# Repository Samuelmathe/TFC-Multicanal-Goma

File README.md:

# TFC Multicanal Goma

Système embarqué IoT de sous-comptage électrique multicanal (ESP32),
développé dans le cadre d'un Travail de Fin de Cycle (ULPGL) : un boîtier
mesure et facture séparément la consommation électrique de plusieurs
locataires branchés sur une même installation, avec coupure automatique par
crédit prépayé et consultation via une application mobile Flutter.

## État du projet

- **Maquette physique** : construite, soudée sur carte perforée et
  **validée sur matériel réel** (4 canaux : 1 bailleur + 3 locataires,
  capteurs simulés par des potentiomètres). C'est cette maquette qui a servi
  à la validation présentée dans le mémoire.
- **Application mobile Flutter** : développée et testée en conditions
  réelles (connexion Wi-Fi à l'ESP32 depuis un téléphone Android).
- **PCB (circuit imprimé, 8 canaux, capteurs ACS712/ZMPT101B réels)** :
  conçu et **routé** sous KiCad (dossier `kicad/`). Carte **compactée le
  19/11/2026 : 138 x 349,5 mm** au lieu de 260 x 440 mm (−58 % de surface),
  re-routée avec Freerouting (scripts `kicad/tools/compact_pcb.py`,
  `route_pcb.py`, `finish_acs712.py`, `cleanup_after_route.py`). Les 17
  borniers restent sur le bord droit ; le HLK-PM01 et le ZMPT101B sont
  regroupés près de l'entrée secteur J10.
  Ajouts du 19/11/2026 : ponts diviseurs 10 k / 12 k (R6-R23) entre les
  capteurs 5 V et les entrées ADC de l'ESP32 ; 32 points d'accueil pour les
  barres de cuivre qui portent le courant de puissance (20 A) ; entrée
  secteur du ZMPT101B déportée sur un bornier J27 au pas de 5 mm (le
  connecteur U12 ne porte plus que GND / VCC / OUT).
  Dernier DRC (KiCad 10.0.8, 19/11/2026) : **0 élément non connecté**,
  7 violations, toutes cosmétiques (empreintes modifiées localement) ;
  plus aucun écart de dégagement 230 V. Détails : `kicad/COMPACTAGE_PCB.md`.
  Les liaisons très proches sur les broches du ACS712 sont couvertes par
  `multical.kicad_dru` (les deux côtés du shunt sont au même potentiel).
  **Non fabriqué ni assemblé** : les Gerbers de `kicad/multical/fabrication/`
  ont été régénérés pour la carte compacte. Le firmware cible
  (`firmware_pcb_capteurs_reels/`) est écrit et compile, mais n'a pas pu
  être testé sur matériel réel.
- **Boîtier 3D** (`boitier/multicanal_boitier.scad`, OpenSCAD) : boîtier
  paramétrique pour le PCB, avec rampe inclinée sur les borniers et
  étiquettes gravées (BAI, LOC1 à LOC7, NEUTRE). Cotes mises à jour pour la
  carte compacte.

## Structure du dépôt

```
firmware/                      -> firmware de la maquette physique (4 canaux,
                                   potentiometres) - construit et valide
firmware_pcb_capteurs_reels/    -> firmware cible pour le PCB (8 canaux,
                                    ACS712 + ZMPT101B) - PCB pas encore
                                    fabrique, code non teste sur materiel reel
application/                     -> application mobile Flutter (Android/iOS)
kicad/                            -> conception du circuit imprime (PCB, 8 canaux)
boitier/                          -> boitier 3D du PCB (OpenSCAD)
rapport/                           -> memoire de TFC
presentation/                       -> support de soutenance
```

Chaque dossier de firmware a son propre `README.md` avec le détail de ce qui
a été testé ou non.

## Démarrer

- Firmware maquette : `cd firmware && pio run --target upload` (ESP32 branché
  en USB) — voir `GUIDE_ASSEMBLAGE_ET_FLASH.md` et `GUIDE_MAQUETTE_BOITIER.md`
  à la racine pour le montage physique.
- Application mobile : `cd application && flutter run` (ou `build_apk.sh`
  pour générer un APK).

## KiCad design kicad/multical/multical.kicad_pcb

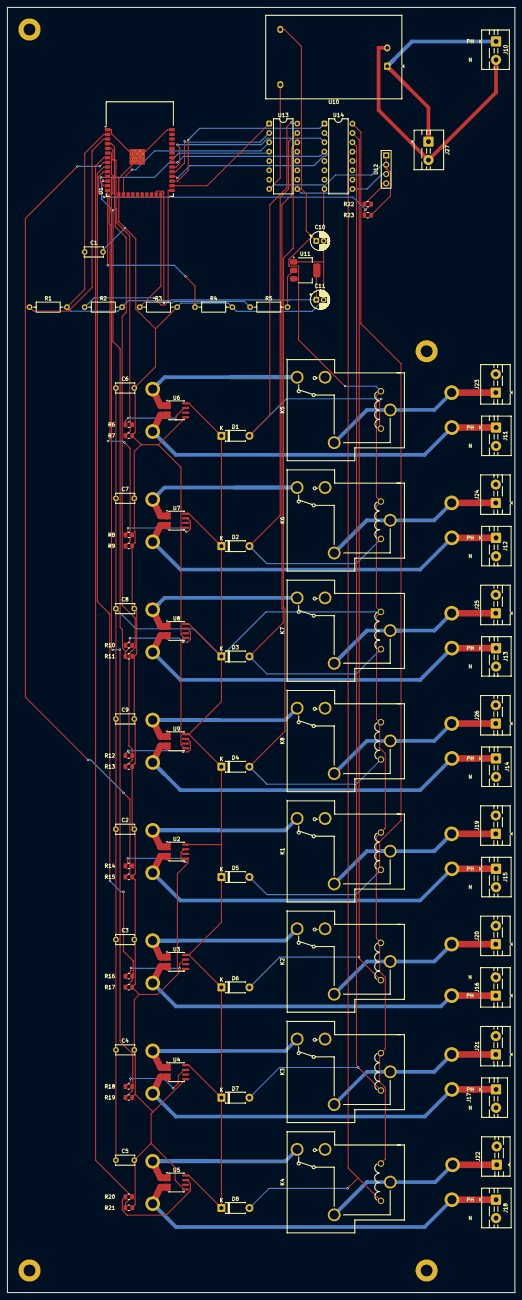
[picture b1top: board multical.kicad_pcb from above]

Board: 2 copper layers, 138.0 x 349.5 mm, 118 parts (0 on the bottom side), 68 nets.

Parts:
BAR1, BAR2, BAR3, BAR4, BAR5, BAR6, BAR7, BAR8, BAR9, BAR10, BAR11, BAR12, BAR13, BAR14, BAR15, BAR16, BAR17, BAR18, BAR19, BAR20, BAR21, BAR22, BAR23, BAR24, BAR25, BAR26, BAR27, BAR28, BAR29, BAR30, BAR31, BAR32: Point barre cuivre; Point_barre_cuivre
C1, C2, C3, C4, C5, C6, C7, C8, C9: C; C_Disc_D5.0mm_W2.5mm_P5.00mm
C10, C11: C; CP_Radial_D5.0mm_P2.00mm
D1, D2, D3, D4, D5, D6, D7, D8: D; D_DO-41_SOD81_P7.62mm_Horizontal
J10, J11, J12, J13, J14, J15, J16, J17, J18, J19, J20, J21, J22, J23, J24, J25, J26: Screw_Terminal_01x02; TerminalBlock_MaiXu_MX126-5.0-02P_1x02_P5.00mm
J27: ZMPT_secteur; TerminalBlock_MaiXu_MX126-5.0-02P_1x02_P5.00mm
K1, K2, K3, K4, K5, K6, K7, K8: Songle_SLA-05VDC-SL-C_LCSC-C87367; RELAY-TH_SLA-XXVDC-XX-C
MH1, MH2, MH3, MH4: MountingHole_3.2mm; MountingHole_3.2mm_NPTH
R1, R2, R3, R4, R5: R; R_Axial_DIN0207_L6.3mm_D2.5mm_P10.16mm_Horizontal
R6, R8, R10, R12, R14, R16, R18, R20, R22: 10k; R_0805_2012Metric
R7, R9, R11, R13, R15, R17, R19, R21, R23: 12k; R_0805_2012Metric
U1: ESP32-WROOM-32
U2, U3, U4, U5, U6, U7, U8, U9: ACS712xLCTR-20A; SOIC-8_3.9x4.9mm_P1.27mm
U10: HLK-PM01; Converter_ACDC_Hi-Link_HLK-PMxx
U11: AMS1117-3.3; SOT-223-3_TabPin2
U12: zmpt101b; ZMPT101B_Header_1x04
U13, U14: ULN2003A; DIP-16_W7.62mm

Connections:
/ACS1_VOUT: R6.1, U6.7 (VIOUT)
/ACS2_VOUT: R8.1, U7.7 (VIOUT)
/ACS3_VOUT: R10.1, U8.7 (VIOUT)
/ACS4_VOUT: R12.1, U9.7 (VIOUT)
/ACS5_VOUT: R14.1, U2.7 (VIOUT)
/ACS6_VOUT: R16.1, U3.7 (VIOUT)
/ACS7_VOUT: R18.1, U4.7 (VIOUT)
/ACS8_VOUT: R20.1, U5.7 (VIOUT)
/CANAL1_HT: BAR1.1, K5.12, U6.1 (IP+), U6.2 (IP+)
/CANAL1_OUT: BAR2.1, BAR4.1, J11.1, U6.3 (IP-), U6.4 (IP-)
/CANAL2_HT: BAR5.1, K6.12, U7.1 (IP+), U7.2 (IP+)
/CANAL2_OUT: BAR6.1, BAR8.1, J12.1, U7.3 (IP-), U7.4 (IP-)
/CANAL3_HT: BAR9.1, K7.12, U8.1 (IP+), U8.2 (IP+)
/CANAL3_OUT: BAR10.1, BAR12.1, J13.1, U8.3 (IP-), U8.4 (IP-)
/CANAL4_HT: BAR13.1, K8.12, U9.1 (IP+), U9.2 (IP+)
/CANAL4_OUT: BAR14.1, BAR16.1, J14.1, U9.3 (IP-), U9.4 (IP-)
/CANAL5_HT: BAR17.1, K1.12, U2.1 (IP+), U2.2 (IP+)
/CANAL5_OUT: BAR18.1, BAR20.1, J15.1, U2.3 (IP-), U2.4 (IP-)
/CANAL6_HT: BAR21.1, K2.12, U3.1 (IP+), U3.2 (IP+)
/CANAL6_OUT: BAR22.1, BAR24.1, J16.1, U3.3 (IP-), U3.4 (IP-)
/CANAL7_HT: BAR25.1, K3.12, U4.1 (IP+), U4.2 (IP+)
/CANAL7_OUT: BAR26.1, BAR28.1, J17.1, U4.3 (IP-), U4.4 (IP-)
/CANAL8_HT: BAR29.1, K4.12, U5.1 (IP+), U5.2 (IP+)
/CANAL8_OUT: BAR30.1, BAR32.1, J18.1, U5.3 (IP-), U5.4 (IP-)
/EN: R1.1, U1.3 (EN)
/GND: C1.2, C2.2, C3.2, C4.2, C5.2, C6.2, C7.2, C8.2, C9.2, C10.2, C11.2, R3.2, R4.2, R7.2, R9.2, R11.2, R13.2, R15.2, R17.2, R19.2, R21.2, R23.2, U1.1 (GND), U1.15 (GND), U1.38 (GND), U1.39 (GND), U2.5 (GND), U3.5 (GND), U4.5 (GND), U5.5 (GND), U6.5 (GND), U7.5 (GND), U8.5 (GND), U9.5 (GND), U10.3 (-Vout), U11.1 (GND), U12.3, U12.4, U13.8 (GND), U14.8 (GND)
/GPIO4: U1.26 (IO4), U13.1 (I1)
/GPIO5: U1.29 (IO5), U13.2 (I2)
/GPIO13: U1.16 (IO13), U13.3 (I3)
/GPIO14: U1.13 (IO14), U13.4 (I4)
/GPIO16: U1.27 (IO16), U14.1 (I1)
/GPIO17: U1.28 (IO17), U14.2 (I2)
/GPIO18: U1.30 (IO18), U14.3 (I3)
/GPIO19: U1.31 (IO19), U14.4 (I4)
/GPIO25: R22.2, R23.1, U1.10 (IO25)
/GPIO26: R8.2, R9.1, U1.11 (IO26)
/GPIO27: R10.2, R11.1, U1.12 (IO27)
/GPIO32: R14.2, R15.1, U1.8 (IO32)
/GPIO33: R16.2, R17.1, U1.9 (IO33)
/GPIO34: R18.2, R19.1, U1.6 (IO34)
/GPIO35: R20.2, R21.1, U1.7 (IO35)
/GPIO36: R6.2, R7.1, U1.4 (SENSOR_VP)
/GPIO39: R12.2, R13.1, U1.5 (SENSOR_VN)
/IO0: R2.1, U1.25 (IO0)
/IO2: R3.1, U1.24 (IO2)
/IO12: R4.1, U1.14 (IO12)
/IO15: R5.1, U1.23 (IO15)
/NEUTRE_BUS: J10.2, J27.2, U10.2 (AC/N)
/P3V3: C1.1, C11.1, R1.2, R2.2, R5.2, U1.2 (VDD), U11.2 (VO)
/P5V: C2.1, C3.1, C4.1, C5.1, C6.1, C7.1, C8.1, C9.1, C10.1, D1.1 (K), D2.1 (K), D3.1 (K), D4.1 (K), D5.1 (K), D6.1 (K), D7.1 (K), D8.1 (K), K1.A1, K2.A1, K3.A1, K4.A1, K5.A1, K6.A1, K7.A1, K8.A1, U2.8 (VCC), U3.8 (VCC), U4.8 (VCC), U5.8 (VCC), U6.8 (VCC), U7.8 (VCC), U8.8 (VCC), U9.8 (VCC), U10.4 (+Vout), U11.3 (VI), U12.5, U13.9 (COM), U14.9 (COM)
/PHASE_BUS: J10.1, J27.1, U10.1 (AC/L)
/REL1_DRV: D1.2 (A), K5.A2, U13.16 (O1)
/REL2_DRV: D2.2 (A), K6.A2, U13.15 (O2)
/REL3_DRV: D3.2 (A), K7.A2, U13.14 (O3)
/REL4_DRV: D4.2 (A), K8.A2, U13.13 (O4)
/REL5_DRV: D5.2 (A), K1.A2, U14.16 (O1)
/REL6_DRV: D6.2 (A), K2.A2, U14.15 (O2)
/REL7_DRV: D7.2 (A), K3.A2, U14.14 (O3)
/REL8_DRV: D8.2 (A), K4.A2, U14.13 (O4)
/ZMPT_VOUT: R22.1, U12.6
CANAL1_PHASE_IN: BAR3.1, J23.1, K5.11
CANAL2_PHASE_IN: BAR7.1, J24.1, K6.11
CANAL3_PHASE_IN: BAR11.1, J25.1, K7.11
CANAL4_PHASE_IN: BAR15.1, J26.1, K8.11
CANAL5_PHASE_IN: BAR19.1, J19.1, K1.11
CANAL6_PHASE_IN: BAR23.1, J20.1, K2.11
CANAL7_PHASE_IN: BAR27.1, J21.1, K3.11
CANAL8_PHASE_IN: BAR31.1, J22.1, K4.11

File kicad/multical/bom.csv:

"Références","Valeur","Empreinte","Qté"
"C1-C9","100n","Capacitor_THT:C_Disc_D5.0mm_W2.5mm_P5.00mm","9"
"C10,C11","100n","Capacitor_THT:CP_Radial_D5.0mm_P2.00mm","2"
"D1-D8","D","Diode_THT:D_DO-41_SOD81_P7.62mm_Horizontal","8"
"J10-J17,J19-J26","Screw_Terminal_01x02","TerminalBlock:TerminalBlock_MaiXu_MX126-5.0-02P_1x02_P5.00mm","16"
"J18","Screw_Terminal_01x02","TerminalBlock_MaiXu_MX126-5.0-02P_1x02_P5.00mm","1"
"K1-K8","Songle_SLA-05VDC-SL-C_LCSC-C87367","multical_local:RELAY-TH_SLA-XXVDC-XX-C","8"
"R1-R5","10k","Resistor_THT:R_Axial_DIN0207_L6.3mm_D2.5mm_P10.16mm_Horizontal","5"
"U1","ESP32-WROOM-32","RF_Module:ESP32-WROOM-32","1"
"U2-U9","ACS712xLCTR-20A","Package_SO:SOIC-8_3.9x4.9mm_P1.27mm","8"
"U10","HLK-PM01","Converter_ACDC:Converter_ACDC_Hi-Link_HLK-PMxx","1"
"U11","AMS1117-3.3","Package_TO_SOT_SMD:SOT-223-3_TabPin2","1"
"U12","zmpt101b","Connector_PinHeader_2.54mm:PinHeader_1x06_P2.54mm_Vertical","1"
"U13,U14","ULN2003A","Package_DIP:DIP-16_W7.62mm","2"

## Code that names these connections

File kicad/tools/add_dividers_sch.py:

"""Ajoute au schema les ponts diviseurs 10 k / 12 k entre les sorties des
capteurs (alimentes en 5 V) et les entrees ADC de l'ESP32.

Pour chaque capteur : l'etiquette posee sur sa broche de sortie (GPIOxx) est
renommee ACSn_VOUT (ou ZMPT_VOUT) ; deux resistances sont ajoutees dans le bas
de la feuille, reliees par etiquettes :
    ACSn_VOUT --[10k]-- GPIOxx --[12k]-- GND
Rapport 12/22 : 0,5-4,5 V -> 0,27-2,45 V (plage utile de l'ADC a 12 dB).
"""
import re, uuid
from pathlib import Path

SCH = Path(__file__).resolve().parents[1] / "multical" / "multical.kicad_sch"
ROOT_UUID = "58486ab8-8a77-40bd-879b-8044d35a44e6"
FOOTPRINT = "Resistor_SMD:R_0805_2012Metric"

# (capteur, etiquette actuelle sur la broche de sortie (x, y), nouveau nom)
SENSORS = [
    ("U6", "GPIO36", (58.42, 50.8), "ACS1_VOUT"),
    ("U7", "GPIO26", (57.15, 76.2), "ACS2_VOUT"),
    ("U8", "GPIO27", (59.69, 96.52), "ACS3_VOUT"),
    ("U9", "GPIO39", (62.23, 116.84), "ACS4_VOUT"),
    ("U2", "GPIO32", (101.6, 49.53), "ACS5_VOUT"),
    ("U3", "GPIO33", (101.6, 72.39), "ACS6_VOUT"),
    ("U4", "GPIO34", (101.6, 95.25), "ACS7_VOUT"),
    ("U5", "GPIO35", (101.6, 118.11), "ACS8_VOUT"),
    ("U12", "GPIO25", (185.42, 149.86), "ZMPT_VOUT"),
]

s = SCH.read_text(encoding="utf-8")
assert "ACS1_VOUT" not in s, "deja applique"
u = lambda: str(uuid.uuid4())


def fmt(v):
    return f"{v:.2f}".rstrip("0").rstrip(".")


# 1) renommage des etiquettes cote capteur
for ref, old, (x, y), new in SENSORS:
    pat = re.compile(r'\(label "' + old + r'"\s+\(at ' + re.escape(fmt(x)) + r" " + re.escape(fmt(y)) + r" ")
    m = pat.search(s)
    assert m, (ref, old, x, y)
    s = s[:m.start()] + f'(label "{new}"\n\t\t(at {fmt(x)} {fmt(y)} ' + s[m.end():]


def label(name, x, y, angle=0):
    return (f'\t(label "{name}"\n\t\t(at {fmt(x)} {fmt(y)} {angle})\n\t\t(effects\n\t\t\t(font\n\t\t\t\t(size 1.27 1.27)\n'
            f'\t\t\t)\n\t\t\t(justify left)\n\t\t)\n\t\t(uuid "{u()}")\n\t)\n')


def prop(name, value, x, y, hide=False, angle=0, justify=True):
    return (f'\t\t(property "{name}" "{value}"\n\t\t\t(at {fmt(x)} {fmt(y)} {angle})\n'
            + ("\t\t\t(hide yes)\n" if hide else "")
            + '\t\t\t(show_name no)\n\t\t\t(do_not_autoplace no)\n\t\t\t(effects\n\t\t\t\t(font\n\t\t\t\t\t(size 1.27 1.27)\n\t\t\t\t)\n'
            + ("\t\t\t\t(justify left)\n" if justify else "") + "\t\t\t)\n\t\t)\n")


def resistor(ref, value, x, y):
    return ("\t(symbol\n\t\t(lib_id \"Device:R\")\n" f"\t\t(at {fmt(x)} {fmt(y)} 0)\n"
            "\t\t(unit 1)\n\t\t(body_style 1)\n\t\t(exclude_from_sim no)\n\t\t(in_bom yes)\n\t\t(on_board yes)\n"
            "\t\t(in_pos_files yes)\n\t\t(dnp no)\n\t\t(fields_autoplaced yes)\n" f"\t\t(uuid \"{u()}\")\n"
            + prop("Reference", ref, x + 2.54, y - 1.27)
            + prop("Value", value, x + 2.54, y + 1.27)
            + prop("Footprint", FOOTPRINT, x - 1.778, y, hide=True, angle=90, justify=False)
            + prop("Datasheet", "", x, y, hide=True, justify=False)
            + prop("Description", "Resistor", x, y, hide=True, justify=False)
            + f'\t\t(pin "2"\n\t\t\t(uuid "{u()}")\n\t\t)\n\t\t(pin "1"\n\t\t\t(uuid "{u()}")\n\t\t)\n'
            f'\t\t(instances\n\t\t\t(project "multical"\n\t\t\t\t(path "/{ROOT_UUID}"\n\t\t\t\t\t(reference "{ref}")\n'
            "\t\t\t\t\t(unit 1)\n\t\t\t\t)\n\t\t\t)\n\t\t)\n\t)\n")


# 2) resistances + etiquettes dans le bas de la feuille (y 172-196 mm)
blocks = []
X0, DX = 25.4, 19.05
Y_TOP, Y_BOT = 177.8, 189.23            # centres des deux resistances
n = 6
for k, (ref, gpio, _, vout) in enumerate(SENSORS):
    x = X0 + k * DX
    rt, rb = f"R{n}", f"R{n + 1}"
    n += 2
    blocks.append(resistor(rt, "10k", x, Y_TOP))
    blocks.append(resistor(rb, "12k", x, Y_BOT))
    blocks.append(label(vout, x, Y_TOP - 3.81))
    blocks.append(label(gpio, x, Y_TOP + 3.81))
    blocks.append(label(gpio, x, Y_BOT - 3.81))
    blocks.append(label("GND", x, Y_BOT + 3.81))
note = (f'\t(text "Ponts diviseurs 10k / 12k : sorties des capteurs (alimentes en 5 V, 0,5-4,5 V)\\n'
        f'ramenees a 0,27-2,45 V pour les entrees ADC de l\'ESP32 (attenuation 12 dB)"\n'
        f"\t\t(exclude_from_sim no)\n\t\t(at {fmt(X0 - 2.54)} 168.91 0)\n\t\t(effects\n\t\t\t(font\n\t\t\t\t(size 1.27 1.27)\n"
        f"\t\t\t)\n\t\t\t(justify left)\n\t\t)\n\t\t(uuid \"{u()}\")\n\t)\n")
marker = "\t(sheet_instances"
assert s.count(marker) == 1
s = s.replace(marker, "".join(blocks) + note + marker)
SCH.write_text(s, encoding="utf-8", newline="\n")
print(f"{len(SENSORS)} ponts diviseurs ajoutes (R6 a R{n - 1})")

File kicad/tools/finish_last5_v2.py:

import uuid

from pathlib import Path
# Chemins relatifs au depot : fonctionne sous Linux comme sous Windows
MULTICAL = Path(__file__).resolve().parents[1] / "multical"
FILE = str(MULTICAL / "multical.kicad_pcb")

with open(FILE, encoding="utf-8") as f:
    content = f.read()

def seg(x1, y1, x2, y2, width, layer, net):
    return (
        '\t(segment\n'
        f'\t\t(start {x1:.4f} {y1:.4f})\n'
        f'\t\t(end {x2:.4f} {y2:.4f})\n'
        f'\t\t(width {width})\n'
        f'\t\t(layer "{layer}")\n'
        f'\t\t(net "{net}")\n'
        f'\t\t(uuid "{uuid.uuid4()}")\n'
        '\t)\n'
    )

def via(x, y, size, drill, net):
    return (
        '\t(via\n'
        f'\t\t(at {x:.4f} {y:.4f})\n'
        f'\t\t(size {size})\n'
        f'\t\t(drill {drill})\n'
        '\t\t(layers "F.Cu" "B.Cu")\n'
        f'\t\t(net "{net}")\n'
        f'\t\t(uuid "{uuid.uuid4()}")\n'
        '\t)\n'
    )

items = []

# --- CANAL1_OUT : U6 (SMD, pitch 1.27mm -> taper fin) -> via -> B.Cu large -> J11 ---
# x=133 choisi pour eviter la diagonale GPIO36 (B.Cu, se termine a x=130.97)
items.append(seg(127.525, 124.635, 127.525, 125.905, 0.3, "F.Cu", "/CANAL1_OUT"))  # pin3-pin4
items.append(seg(127.525, 125.905, 133.0, 128.0, 0.3, "F.Cu", "/CANAL1_OUT"))       # taper vers via
items.append(via(133.0, 128.0, 0.6, 0.3, "/CANAL1_OUT"))
items.append(seg(133.0, 128.0, 133.0, 110.0, 2.5, "B.Cu", "/CANAL1_OUT"))
items.append(seg(133.0, 110.0, 205.0, 110.0, 2.5, "B.Cu", "/CANAL1_OUT"))
items.append(seg(205.0, 110.0, 205.0, 124.0, 2.5, "B.Cu", "/CANAL1_OUT"))
items.append(seg(205.0, 124.0, 209.0, 124.0, 2.5, "B.Cu", "/CANAL1_OUT"))

# --- CANAL3_OUT : bout de piste existant (B.Cu) -> via -> F.Cu -> U8 pin3/pin4 (SMD F.Cu uniquement) ---
items.append(via(122.9657, 174.4434, 0.6, 0.3, "/CANAL3_OUT"))
items.append(seg(122.9657, 174.4434, 126.0, 174.135, 0.3, "F.Cu", "/CANAL3_OUT"))
items.append(seg(126.0, 174.135, 127.525, 174.135, 0.3, "F.Cu", "/CANAL3_OUT"))
items.append(seg(127.525, 174.135, 127.525, 175.405, 0.3, "F.Cu", "/CANAL3_OUT"))

# --- NEUTRE_BUS : U12 pin2 -> fin (evite pin1 a 2.54mm) -> bus existant pres du HLK ---
items.append(seg(20.0, 47.54, 24.0, 47.54, 0.3, "F.Cu", "/NEUTRE_BUS"))   # sort horizontalement, loin de pin1 (au-dessus)
items.append(seg(24.0, 47.54, 24.0, 20.0, 0.3, "F.Cu", "/NEUTRE_BUS"))
items.append(seg(24.0, 20.0, 155.0, 20.0, 0.3, "F.Cu", "/NEUTRE_BUS"))
items.append(seg(155.0, 20.0, 155.0, 40.0, 0.3, "F.Cu", "/NEUTRE_BUS"))
items.append(seg(155.0, 40.0, 165.0, 40.0, 0.3, "F.Cu", "/NEUTRE_BUS"))

marker = "\t(embedded_fonts no)\n)"
assert content.count(marker) == 1
block = "\n" + "".join(items)
content = content.replace(marker, block + marker)

with open(FILE, "w", encoding="utf-8") as f:
    f.write(content)

print(f"OK: {len(items)} elements ajoutes")
